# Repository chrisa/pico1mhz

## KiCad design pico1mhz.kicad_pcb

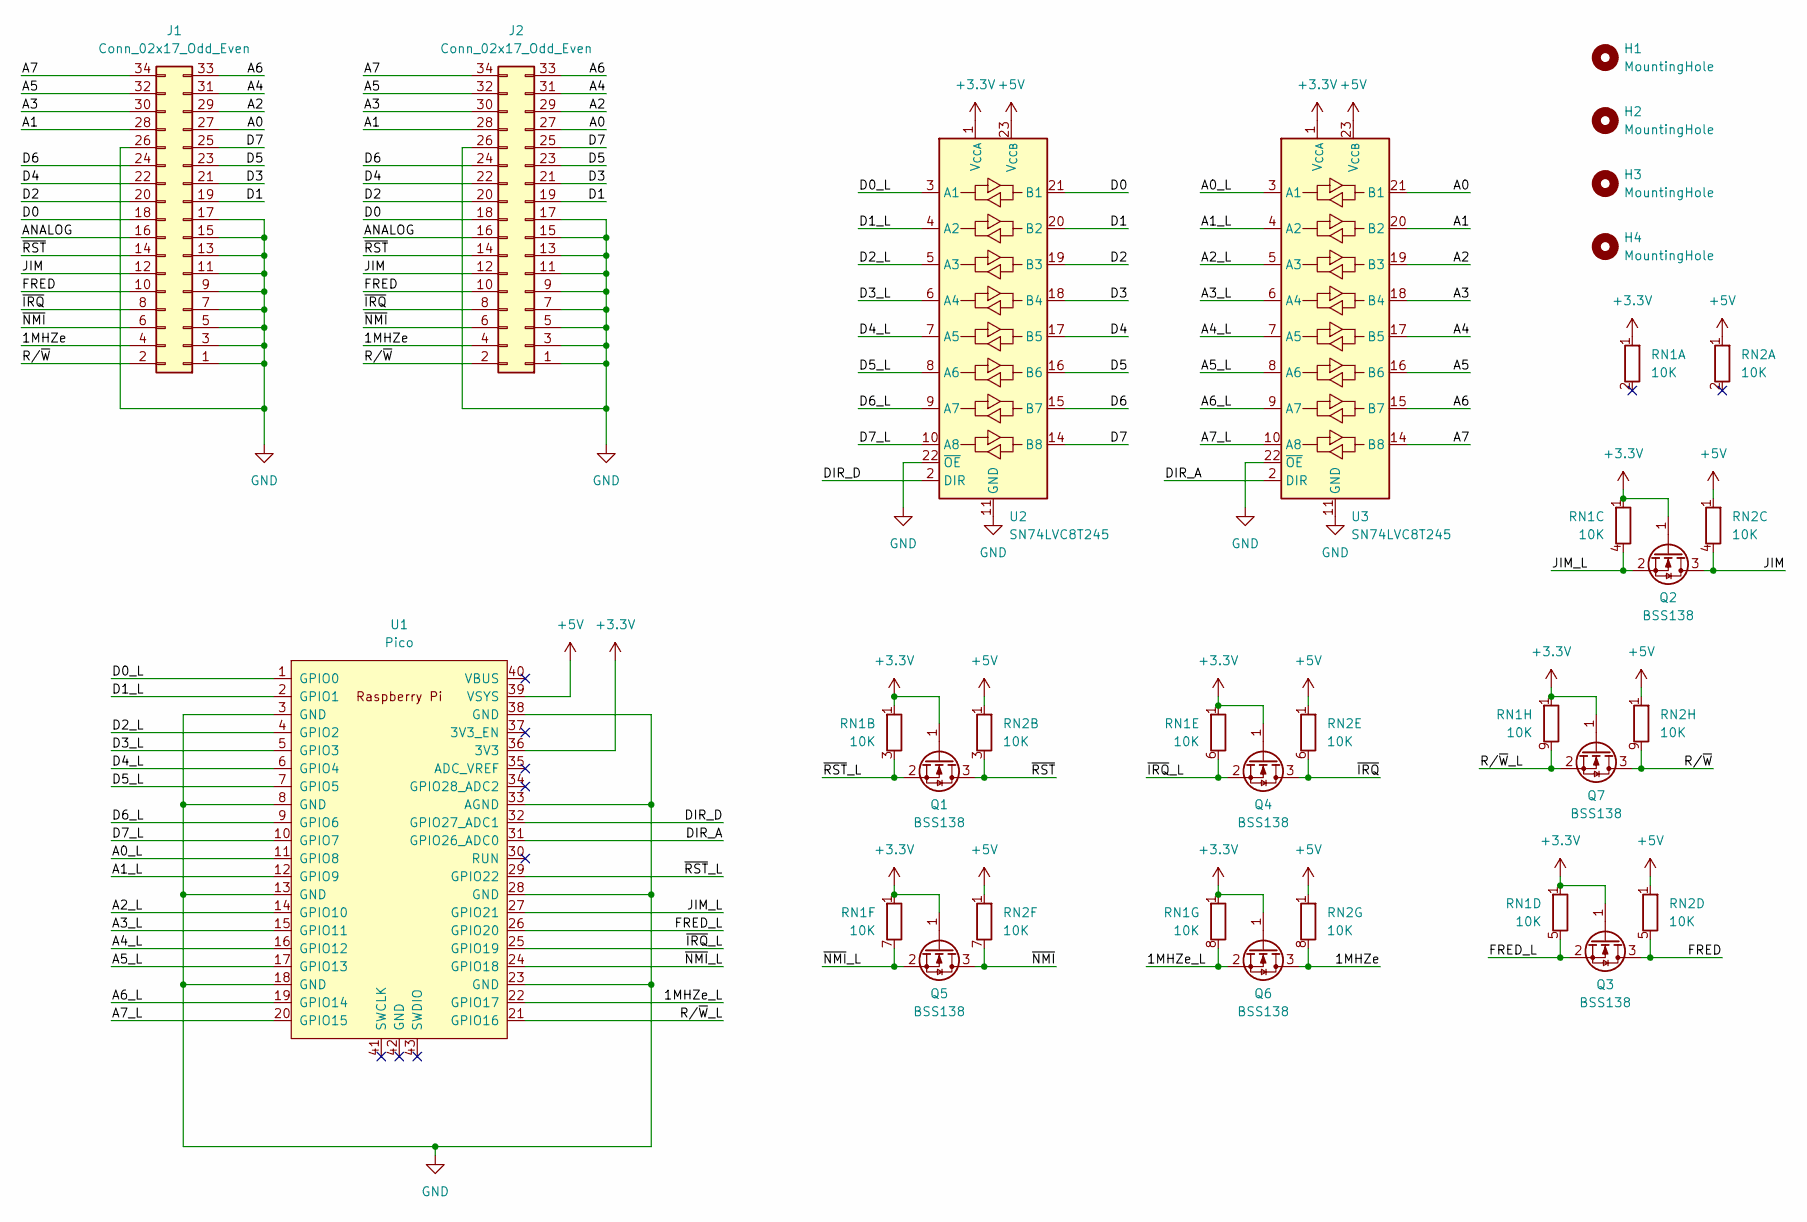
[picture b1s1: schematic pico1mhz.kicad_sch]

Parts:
H1, H2, H3, H4: MountingHole; MountingHole_3.2mm_M3
J1, J2: Conn_02x17_Odd_Even; PinHeader_2x17_P2.54mm_Vertical
Q1, Q2, Q3, Q4, Q5, Q6, Q7: BSS138; SOT-23
RN1, RN2: 10K; R_Array_SIP9
U1: Pico; RPi_Pico_SMD_TH
U2, U3: SN74LVC8T245; SOIC-24W_7.5x15.4mm_P1.27mm

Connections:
+3.3V: Q1.1 (G), Q2.1 (G), Q3.1 (G), Q4.1 (G), Q5.1 (G), Q6.1 (G), Q7.1 (G), RN1.1 (R1), U1.36 (3V3), U2.1 (V_{CCA}), U3.1 (V_{CCA})
+5V: RN2.1 (R1), U1.39 (VSYS), U2.23 (V_{CCB}), U2.24 (V_{CCB}), U3.23 (V_{CCB}), U3.24 (V_{CCB})
/1MHZe: J1.4, J2.4, Q6.3 (D), RN2.8 (R7.2)
/1MHZe_L: Q6.2 (S), RN1.8 (R7.2), U1.22 (GPIO17)
/A0: J1.27, J2.27, U3.21 (B1)
/A0_L: U1.11 (GPIO8), U3.3 (A1)
/A1: J1.28, J2.28, U3.20 (B2)
/A1_L: U1.12 (GPIO9), U3.4 (A2)
/A2: J1.29, J2.29, U3.19 (B3)
/A2_L: U1.14 (GPIO10), U3.5 (A3)
/A3: J1.30, J2.30, U3.18 (B4)
/A3_L: U1.15 (GPIO11), U3.6 (A4)
/A4: J1.31, J2.31, U3.17 (B5)
/A4_L: U1.16 (GPIO12), U3.7 (A5)
/A5: J1.32, J2.32, U3.16 (B6)
/A5_L: U1.17 (GPIO13), U3.8 (A6)
/A6: J1.33, J2.33, U3.15 (B7)
/A6_L: U1.19 (GPIO14), U3.9 (A7)
/A7: J1.34, J2.34, U3.14 (B8)
/A7_L: U1.20 (GPIO15), U3.10 (A8)
/ANALOG: J1.16, J2.16
/D0: J1.18, J2.18, U2.21 (B1)
/D0_L: U1.1 (GPIO0), U2.3 (A1)
/D1: J1.19, J2.19, U2.20 (B2)
/D1_L: U1.2 (GPIO1), U2.4 (A2)
/D2: J1.20, J2.20, U2.19 (B3)
/D2_L: U1.4 (GPIO2), U2.5 (A3)
/D3: J1.21, J2.21, U2.18 (B4)
/D3_L: U1.5 (GPIO3), U2.6 (A4)
/D4: J1.22, J2.22, U2.17 (B5)
/D4_L: U1.6 (GPIO4), U2.7 (A5)
/D5: J1.23, J2.23, U2.16 (B6)
/D5_L: U1.7 (GPIO5), U2.8 (A6)
/D6: J1.24, J2.24, U2.15 (B7)
/D6_L: U1.9 (GPIO6), U2.9 (A7)
/D7: J1.25, J2.25, U2.14 (B8)
/D7_L: U1.10 (GPIO7), U2.10 (A8)
/DIR_A: U1.31 (GPIO26_ADC0), U3.2 (DIR)
/DIR_D: U1.32 (GPIO27_ADC1), U2.2 (DIR)
/FRED: J1.10, J2.10, Q3.3 (D), RN2.5 (R4.2)
/FRED_L: Q3.2 (S), RN1.5 (R4.2), U1.26 (GPIO20)
/JIM: J1.12, J2.12, Q2.3 (D), RN2.4 (R3.2)
/JIM_L: Q2.2 (S), RN1.4 (R3.2), U1.27 (GPIO21)
/R/~W: J1.2, J2.2, Q7.3 (D), RN2.9 (R8.2)
/R/~W_L: Q7.2 (S), RN1.9 (R8.2), U1.21 (GPIO16)
/~IRQ: J1.8, J2.8, Q4.3 (D), RN2.6 (R5.2)
/~IRQ_L: Q4.2 (S), RN1.6 (R5.2), U1.25 (GPIO19)
/~NMI: J1.6, J2.6, Q5.3 (D), RN2.7 (R6.2)
/~NMI_L: Q5.2 (S), RN1.7 (R6.2), U1.24 (GPIO18)
/~RST: J1.14, J2.14, Q1.3 (D), RN2.3 (R2.2)
/~RST_L: Q1.2 (S), RN1.3 (R2.2), U1.29 (GPIO22)
GND: J1.1, J1.3, J1.5, J1.7, J1.9, J1.11, J1.13, J1.15, J1.17, J1.26, J2.1, J2.3, J2.5, J2.7, J2.9, J2.11, J2.13, J2.15, J2.17, J2.26, U1.3 (GND), U1.8 (GND), U1.13 (GND), U1.18 (GND), U1.23 (GND), U1.28 (GND), U1.33 (AGND), U1.38 (GND), U2.11 (GND), U2.12 (GND), U2.13 (GND), U2.22 (~OE), U3.11 (GND), U3.12 (GND), U3.13 (GND), U3.22 (~OE)

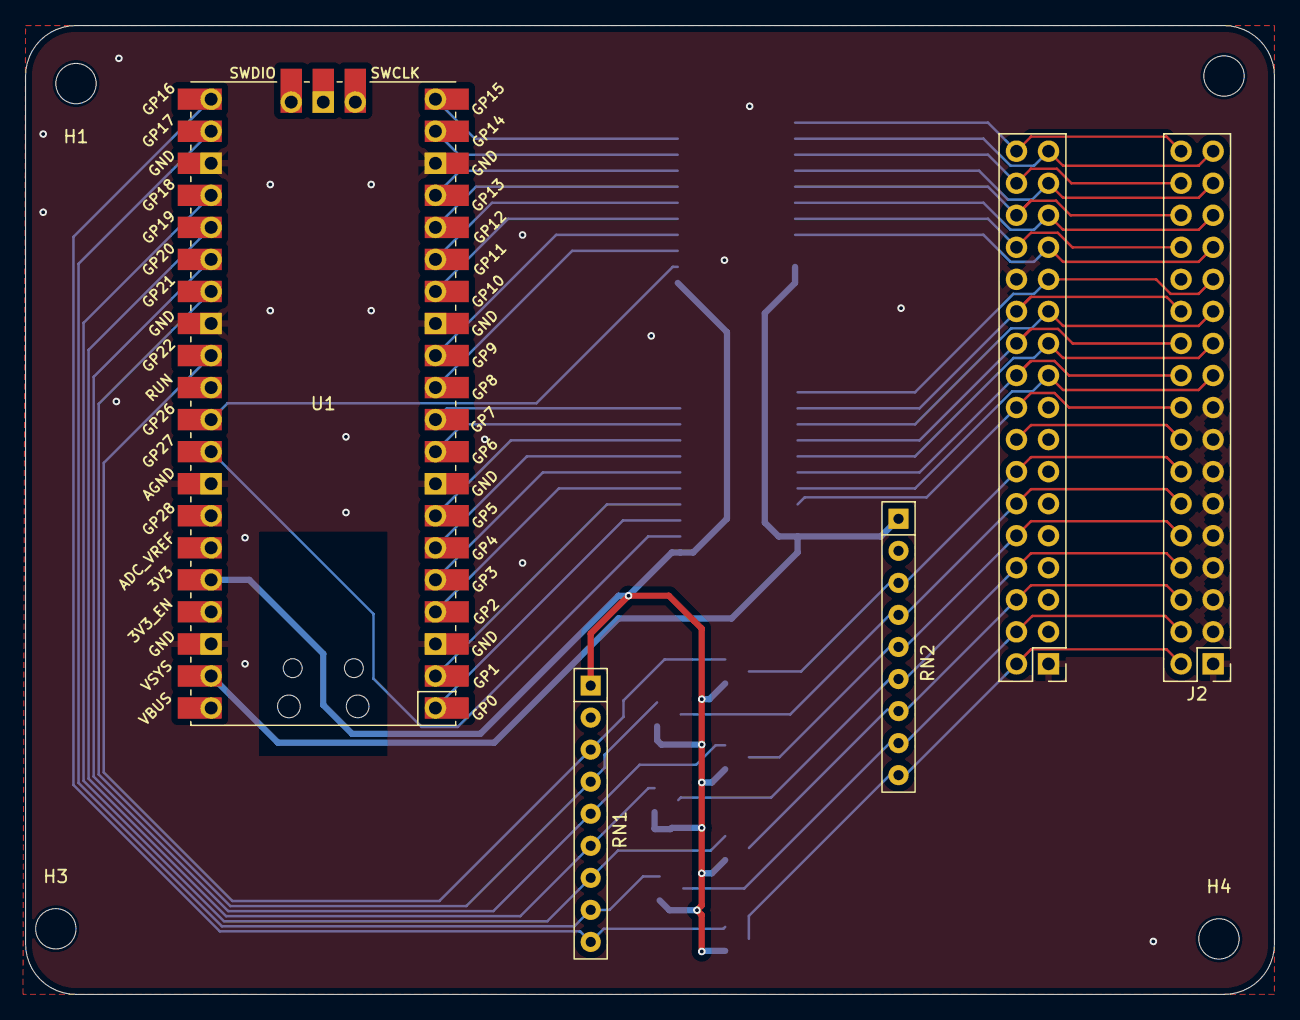
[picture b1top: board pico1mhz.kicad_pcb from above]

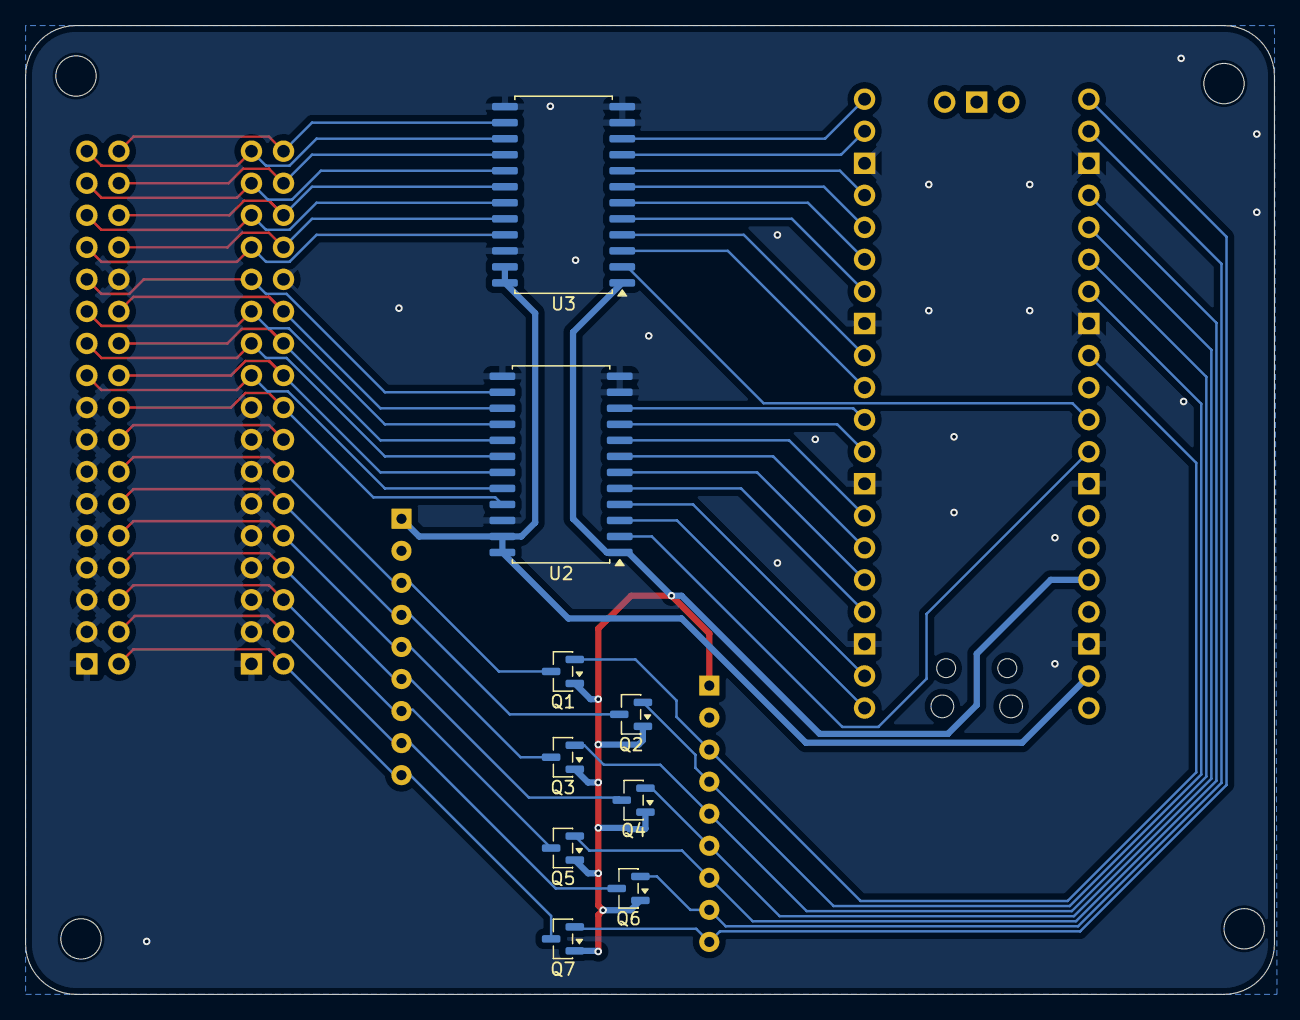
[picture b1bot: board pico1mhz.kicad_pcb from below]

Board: 2 copper layers, 99.0 x 76.8 mm, 18 parts (9 on the bottom side), 52 nets.

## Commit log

2026-02-08 initial, too big
2026-02-08 Smaller, less than 100mm
2026-02-08 fixup after size change
2026-02-08 Adjust for JLC design rules
